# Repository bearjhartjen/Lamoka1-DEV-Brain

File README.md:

<h1 align="center">
  
  <br>
  Lamoka1-DEV-Brain
</h1>

<p align="center">
  This board can now be ordered
  <a href="https://www.pcbway.com/project/shareproject/Lamoka1_DEV_Brain_49e4fd0a.html">here</a>.
</p>

<p align="center">
  PIE versions v1.8 and below will function on this board.
  For more information on PIE, go
  <a href="SOFTWARE/README.md">here</a>.
</p>

<p align="center">
  <a href="https://htmlpreview.github.io/?https://raw.githubusercontent.com/bearjhartjen/Lamoka1-DEV-Brain/master/HARDWARE/Kicad%20files/BOM/Lamoka1-DEV-Brain.html">
    <strong>View Interactive BOM</strong>
  </a>
</p>

---

## What this board is

The DEV-Brain brings the Lamoka1's MCU, lights and simplicity into a 70 × 30 mm
laminated sandwich (PCB). It carries the RP2354A microcontroller, one button,
ten addressable RGB LEDs (D1–D10) and a USB-C port.

It is a **prototype of the Lamoka1's control section**, and a product in its own
respect. We develop the PIE firmware on it, because
the control side is a big driver to the creativity and flexability of our products, and because it means we can
work on the lights and the button without ever having the power stage on the
bench, lowering risk and cost for development. 

Flamingo and Cactus have paid PCBWay to manufacture and assemble the DEV-Brain.
It has arrived and works much better than expected.

This board was run through Tomachie to get the design checked; the link is
[here](https://tomachie.com/r/a1f3f256-a8ca-43de-aa92-e70ef981c3c2/Lamoka1-DEV-board_report.html#design-summary).

## How to order your own 

We have published the board to PCBWay's share projects platform
[here](https://www.pcbway.com/project/shareproject/Lamoka1_DEV_Brain_49e4fd0a.html).
There, you will be able to order the Lamoka1-DEV-Brain exactly as we did.

## Tests

We were able to run the Lamoka1-DEV-Brain for 72 hours running the idle blue dot bouncing animation seen in [PIE v1.8](SOFTWARE/Portal%20Interface%20Engine/V1.8.ino). The environment was an average of 70 degrees Fahrenheit, and an average humidity of 70 percent. We stopped the test early (there were no signs of issues) because we needed to use the Lamoka1-DEV-Brain to test the HTML file creation concept for getting diagnostic data off of the Lamoka1.

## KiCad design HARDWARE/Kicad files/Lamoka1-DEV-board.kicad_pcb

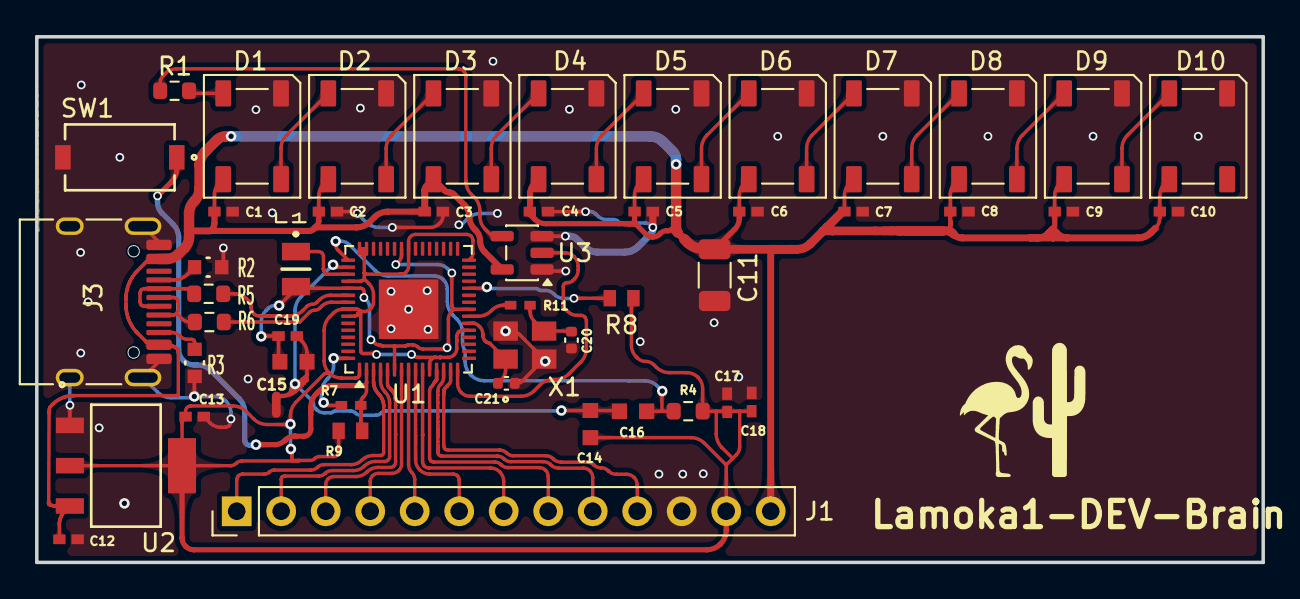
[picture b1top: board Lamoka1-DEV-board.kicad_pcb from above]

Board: 2 copper layers, 70.0 x 30.0 mm, 50 parts (0 on the bottom side), 41 nets.

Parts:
C1, C2, C3, C4, C5, C6, C7, C8, C9, C10, C17, C18, C19: 100n; CAP_0402_SAM
C11: 100u; C_1206_3216Metric
C12, C13: 10u; CAP_CL_05_SAM
C14, C15, C16: 4.7u; CAP_0603_CL10A_1P6XP8_SAM
C20, C21: 15p; C_0402_1005Metric
D1, D2, D3, D4, D5, D6, D7, D8, D9, D10: WS2812B; LED_WS2812B_PLCC4_5.0x5.0mm_P3.2mm
J1: Conn_01x13_Pin; PinHeader_1x13_P2.54mm_Vertical
J3: USB_C_Receptacle_USB2.0_14P; USB_C_Receptacle_HRO_TYPE-C-31-M-12
L1: 3.3u; AOTAB201610S3R3101T
NT1: NetTie_2; NetTie-2_SMD_Pad0.5mm
R1: 330; R_0603_1608Metric
R2, R3: 5.1k; RC0603N_YAG
R4: 33; R_0603_1608Metric
R5, R6: 27; R_0603_1608Metric
R7, R11: 1k; RC0402N_PAN
R8, R9: 10k; RES_CRCW_0603
SW1: PTS636 SM43J SMTR LFS; SW_PTS636_CNK
U1: RP2354A; QFN-60-1EP_7x7mm_P0.4mm_EP3.4x3.4mm
U2: AMS1117-3.3; SOT-223_UMW
U3: 74AHCT1G125; SOT-23-5
X1: ABM8-272-T3; ABM8-272-T3_ABR

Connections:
/1V1: C15.1, C19.1, L1.2, U1.6 (DVDD), U1.23 (DVDD), U1.39 (DVDD), U1.50 (VREG_FB)
/3V3: C13.1, C14.1, C17.1, C18.1, J1.12, R4.1, R8.1, R9.1, U1.1 (IOVDD), U1.11 (IOVDD), U1.20 (IOVDD), U1.30 (IOVDD), U1.38 (IOVDD), U1.44 (ADC_AVDD), U1.45 (IOVDD), U1.49 (VREG_VIN), U1.53 (USB_OTP_VDD), U1.54 (QSPI_IOVDD), U2.2 (VOUT), U2.4 (VOUT)
/5V: C1.1, C2.1, C3.1, C4.1, C5.1, C6.1, C7.1, C8.1, C9.1, C10.1, C11.1, C12.2, D1.1 (VDD), D2.1 (VDD), D3.1 (VDD), D4.1 (VDD), D5.1 (VDD), D6.1 (VDD), D7.1 (VDD), D8.1 (VDD), D9.1 (VDD), D10.1 (VDD), J1.13, J3.A4 (VBUS), J3.A9 (VBUS), J3.B4 (VBUS), J3.B9 (VBUS), U2.3 (VIN), U3.5 (VCC)
/BTN: R7.1, R9.2, SW1.1, U1.2 (GPIO0)
/GPIO1: J1.1, U1.3 (GPIO1)
/GPIO2: J1.2, U1.4 (GPIO2)
/GPIO3: J1.3, U1.5 (GPIO3)
/GPIO4: J1.4, U1.7 (GPIO4)
/GPIO5: J1.5, U1.8 (GPIO5)
/GPIO6: J1.6, U1.9 (GPIO6)
/GPIO7: J1.7, U1.10 (GPIO7)
/GPIO8: J1.8, U1.12 (GPIO8)
/GPIO9: J1.9, U1.13 (GPIO9)
/GPIO10: J1.10, U1.14 (GPIO10)
/USB_DM: R5.2, U1.51 (USB_DM)
/USB_DP: R6.2, U1.52 (USB_DP)
/VREG_GND: C14.2, C15.2, C16.2, C19.2, NT1.1, U1.47 (VREG_PGND)
/XIN: C21.1, U1.21 (XIN), X1.1
/XOUT: R11.2, U1.22 (XOUT)
GND: C1.2, C2.2, C3.2, C4.2, C5.2, C6.2, C7.2, C8.2, C9.2, C10.2, C11.2, C12.1, C13.2, C17.2, C18.2, C20.2, C21.2, D1.3 (VSS), D2.3 (VSS), D3.3 (VSS), D4.3 (VSS), D5.3 (VSS), D6.3 (VSS), D7.3 (VSS), D8.3 (VSS), D9.3 (VSS), D10.3 (VSS), J1.11, J3.A1 (GND), J3.A12 (GND), J3.B1 (GND), J3.B12 (GND), J3.SH (SHIELD), NT1.2, R2.2, R3.2, SW1.2, U1.61 (GND), U2.1 (GND), U3.1, U3.3 (GND), X1.2, X1.4
unnamed: C20.1, R11.1, X1.3
unnamed: D1.4 (DIN), R1.1
unnamed: D1.2 (DOUT), D2.4 (DIN)
unnamed: D2.2 (DOUT), D3.4 (DIN)
unnamed: D3.2 (DOUT), D4.4 (DIN)
unnamed: D4.2 (DOUT), D5.4 (DIN)
unnamed: D5.2 (DOUT), D6.4 (DIN)
unnamed: D6.2 (DOUT), D7.4 (DIN)
unnamed: D7.2 (DOUT), D8.4 (DIN)
unnamed: D8.2 (DOUT), D9.4 (DIN)
unnamed: D9.2 (DOUT), D10.4 (DIN)
unnamed: J3.A5 (CC1), R2.1
unnamed: J3.B5 (CC2), R3.1
unnamed: J3.A6 (D+), J3.B6 (D+), R6.1
unnamed: J3.A7 (D-), J3.B7 (D-), R5.1
unnamed: R1.2, U3.4
unnamed: U1.15 (GPIO11), U3.2
unnamed: R8.2, U1.26 (RUN)
unnamed: C16.1, R4.2, U1.46 (VREG_AVDD)
unnamed: L1.1, U1.48 (VREG_LX)
unnamed: R7.2, U1.60 (~QSPI_SS)
